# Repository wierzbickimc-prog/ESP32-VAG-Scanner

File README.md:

# ESP32 VAG Scanner

Read older VW and Audi controllers with a cheap KKL USB cable. Scan the car's modules, read
identification, read and clear fault codes, and watch live measuring blocks. It speaks
**KW1281**, the K-line protocol used by VAG cars from about 1990 to 2004.

There are two front ends, both driving the same cable with the same protocol core:

- **macOS**: a SwiftUI app.
- **ESP32-P4**: a standalone touch-screen unit (Guition JC8012P4A1C). The KKL cable plugs
  into the P4's USB port, with no wiring.

> **Status:** tested on a 2002 EuroVan from the Mac: the engine (Motronic ME7.1, 10400 baud)
> and the 01P automatic transmission (1200 baud) read identification, faults and live data.
> The P4 runs on hardware; its first real-car test is under way. Other cars and controllers
> are untested.

## Install on an ESP32-P4 (no tools needed)

Open the **[install page](https://wierzbickimc-prog.github.io/ESP32-VAG-Scanner/)** in Chrome or
Edge, connect the board's USB-serial port, and click **Install**. It uses
[ESP Web Tools](https://esphome.github.io/esp-web-tools/). Each GitHub release builds the firmware
and updates the page automatically (`.github/workflows/firmware.yml`).

## Screenshots

### macOS

| Overview | Fault codes |
|---|---|
|  |  |

Click a fault for everything the controller stores about it:

### ESP32-P4

| Home | Fault codes |
|---|---|
|  |  |

### Dashboard

| macOS | ESP32-P4 |
|---|---|
|  |  |

All screenshots show the simulated EuroVan (demo mode).

## Features

- Open a module directly from the landing screen and automatically read its fault codes,
  without scanning the car first. Both apps show **01 Engine**, **02 Transmission**,
  **03 ABS**, **08 HVAC**, **15 Airbags**, and **17 Instruments**, with **More modules** for
  the remaining known addresses. Identification and faults use one connection.
- Scan for controllers (common addresses, or all of 01-7F).
- Controller identification (part number, component, coding).
- Fault codes with descriptions, OBD-II P-codes, the fault type ("Short to Ground") and the
  intermittent flag. Clearing asks for confirmation first.
- Live measuring blocks, with standard VW labels where known.
- A **four-slot dashboard** with live values and trend charts. The EuroVan default shows
  coolant temperature, battery voltage, ATF temperature and fuel economy. Each slot can show
  a preset, or any field you pin from a controller's Live data (the pin button on the Mac;
  tap the value on the P4). US or metric units.
- Fault codes link to the **Ross-Tech wiki**. The Mac opens the page in the browser. The P4
  shows a QR code, and with **Wi-Fi** (through the board's ESP32-C6) reads the page itself.
- **Fuel economy** estimated from the engine's air mass and vehicle speed (VW standard groups
  2 and 5, assuming a stoichiometric mixture), with instant and trip average. On the Mac,
  **Calibrate** scales the estimate to match the fuel actually pumped at a fill-up.
- Recognises a few specific cars from their part numbers (T4 EuroVan, Mk3 Golf) and shows a
  matching photo.
- Demo mode with simulated cars, so you can try it without a car or cable.
- **EuroVan health checks** on both apps: a guided 01P ATF level assistant,
  AXK camshaft timing/chain assessment, misfire-counter monitoring and an ECU
  supply-voltage check. Each shows its prerequisites, readings, limitations and
  factory procedure source, and can save a local snapshot. See
  [procedures and validation status](docs/health-checks.md).

Connecting the cable does not start vehicle communication. Tap **Scan car** or a
module card to begin; the ESP32 also stays idle if its display cannot initialize.

The **Scan car** button still discovers controllers as before. Module cards start at
**Not checked** and update after a read; a missing controller shows **No response** rather
than a clean fault result. Not every car has every controller. Addresses use hexadecimal
notation (for example, **17** means instruments).

**Dashboard notes.** KW1281 talks to one controller at a time, and switching costs a 2–3 s
wake-up. The dashboard reads each controller several times before switching, so slots on
the engine update continuously while the transmission's ATF temperature updates every few
seconds. The ATF preset uses **02, group 5, field 1**, verified on the EuroVan's 01P.
Some other transmissions use group 2 or 4: open **02 Auto Trans → Live data**,
find the temperature, and pin it to the slot if it differs.
You can start the dashboard directly without opening a module or scanning first.
Its first connection to each controller retries wake-up and searches the supported
baud rates even if no sync byte arrives. This initial discovery can take longer
than a normal controller switch; absent controllers get a short retry on later visits.
Tiles show connection status and the age of the last successful sample, including
when a failed read leaves the previous value displayed.
The fuel estimate can't see overrun fuel cut-off, so calibrate it after a fill-up.

For connection diagnostics on the Mac, run `KW_TRACE=1 swift run ESP32VAGScanner`
from `mac/`. The trace includes address, attempted baud, cached baud, sync byte
or timeout, handshake/identification phase, and error code. The P4 emits these
connection diagnostics in its serial monitor, plus measuring-group failures.

KW1281 controllers store only a fault code and one status byte. There's no mileage,
occurrence count or freeze-frame data; that arrived with KWP2000 and UDS, which this tool
doesn't support.

**Health checks.** Open **Health checks** in the Mac sidebar or **EuroVan health
checks** on the P4 home screen. Choose a check, Start, then confirm the physical
conditions for that run. The ATF assistant requires a cold start around 30°C or
below and guides a physical overflow inspection at 35–45°C; the app cannot
measure fluid level. Timing screening applies the verified AXK intake limits and
shows the exhaust offset and difference as observations. It does not certify
chain or guide condition. Checks are restricted to engine `022906032AF` and
transmission `01P927733CG`; new health groups still await real-vehicle validation.

## Hardware

- A **KKL USB cable with an FTDI chip** (`0403:6001`, FT232R/BM). Tested cable: "USB <-> Serial",
  no serial number.
- For the standalone unit: a **Guition JC8012P4A1C** (ESP32-P4, 10.1" 800x1280 touch screen).

## Layout

| Path | What |
|---|---|
| [`kwcore/`](kwcore) | KW1281 protocol in plain C99, a simulated ECU, tests, and the `kwcli` command-line tool |
| [`mac/`](mac) | SwiftUI app. It links `kwcore` through symlinks in `Sources/KWCore` |
| [`esp32/`](esp32) | ESP-IDF project: USB host FTDI driver, LVGL UI. See [`esp32/README.md`](esp32/README.md) |
| [`hardware/kline-dongle/`](hardware/kline-dongle) | Unbuilt ESP32-C3 K-line dongle prototype; circuit, PCB, and assembly notes. Dedicated firmware is pending |
| [`assets/`](assets) | Car photos, measuring-block labels, and the scripts that build and fetch them |
| [`kw1281test/`](https://github.com/gmenounos/kw1281test) | Submodule: the upstream C# tool this protocol code is checked against |
| [`HANDOVER.md`](HANDOVER.md) | Design decisions, verified facts, and next steps |

## Build and run

```sh
git clone --recursive https://github.com/wierzbickimc-prog/ESP32-VAG-Scanner.git
cd ESP32-VAG-Scanner
```

**Protocol tests and command-line tool**

```sh
make -C kwcore test
make -C kwcore kwcli
kwcore/kwcli /dev/cu.usbserial-XXXX scan
kwcore/kwcli /dev/cu.usbserial-XXXX faults 01   # addresses are hex: 17 = instruments
KW_TRACE=1 kwcore/kwcli /dev/cu.usbserial-XXXX ident 01   # log every byte
```

**macOS app** (macOS 13+, Swift 5.9+)

```sh
cd mac
swift run ESP32VAGScanner                   # pick the cable in the app
swift run ESP32VAGScanner --demo            # straight into the simulated EuroVan
swift run ESP32VAGScanner --demo=golf --overview
swift run ESP32VAGScanner --demo --dashboard  # simulated EuroVan, dashboard running
swift run ESP32VAGScanner --demo --health     # EuroVan health-check screen
```

Direct-module integration tests use the simulated cars and require Xcode's XCTest framework:

```sh
DEVELOPER_DIR=/Applications/Xcode.app/Contents/Developer swift test --package-path mac
```

**ESP32-P4** (ESP-IDF v5.5.6)

```sh
. ~/esp/esp-idf-v5.5/export.sh
cd esp32
idf.py build
idf.py -p /dev/cu.usbserial-XXXX flash monitor   # the board's CH340 port
```

On the P4, hold **Scan** to open the demo cars. **Dashboard** sits between Scan and Demo. The
Wi-Fi button at the top opens the Wi-Fi screen; Wi-Fi is only used for the wiki viewer.

## Optional data (not in this repo)

Both apps work without these. With them, faults get descriptions and type text. Released P4
firmware includes the fault type names but never the Ross-Tech descriptions; it reads those
from the Ross-Tech wiki over Wi-Fi instead.

- **Fault descriptions:** a `code,meaning` CSV saved as `ross-tech-fault-codes.csv` in the repo
  root (the P4 build embeds it), and on the Mac as
  `~/Library/Application Support/ESP32 VAG Scanner/fault-codes.csv`.
- **Fault type names:** `python3 assets/tools/fetch_fault_types.py` downloads the list from
  [KLineKWP1281Lib_ESP32](https://github.com/domnulvlad/KLineKWP1281Lib_ESP32) (GPL-3.0) at a
  pinned commit into `kwcore/fault_types.h`. On the Mac, run `touch kwcore/fault_table.c` before
  the next build so it picks the file up.

## License

GNU General Public License v3.0 (see [`LICENSE`](LICENSE)): use it, share it, and change it
freely, and pass the same freedom on with anything you distribute. The fault type names come
from GPL-3.0 code. Bundled third-party parts keep their own licences (MIT and Apache-2.0, all
compatible), and the car photos are CC-licensed as listed in `assets/CREDITS.md`. Not affiliated
with Volkswagen or Ross-Tech.

## Credits

- Protocol behaviour follows [kw1281test](https://github.com/gmenounos/kw1281test) by Greg
  Menounos (MIT).
- Display and touch drivers are vendored from
  [chipguyhere/JC8012P4A1C_display](https://github.com/chipguyhere/JC8012P4A1C_display) (MIT).
- Fault type names come from [KLineKWP1281Lib_ESP32](https://github.com/domnulvlad/KLineKWP1281Lib_ESP32)
  by domnulvlad (GPL-3.0); header+body measuring-group formulas follow the same library.
- Car photos come from Wikimedia Commons; authors and licences are in
  [`assets/CREDITS.md`](assets/CREDITS.md) and shown in both apps.

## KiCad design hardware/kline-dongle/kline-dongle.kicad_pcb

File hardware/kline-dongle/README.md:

# K-line dongle (revision 3 prototype)

A 58 × 24 mm, two-layer carrier for a Seeed XIAO ESP32C3 and an ST L9637D
K-line transceiver, in a 3D-printed case. Open `kline-dongle.kicad_pro` in KiCad 10.

**Status: unbuilt prototype.** ERC, DRC and schematic parity are clean, and the case
has been checked against the board's 3D model. Nothing has been built. Bench
operation, case fit and tolerances, automotive transients, temperature and RF
performance are not validated. This is a **12 V vehicle design**: don't use it on a
24 V vehicle or assume it survives a 24 V jump start.

**Firmware is still required.** The repository's ESP32 firmware targets the P4
display and an FTDI cable; it does not run on this C3 dongle. A direct-UART `KwIo`,
battery measurement and a BLE/Wi-Fi link are still to be written. The pin table
below is their hardware interface.

## Revision 3 changes

- **U1 lies flat.** The upright R-78HB stood 17.5 mm tall; the horizontal
  R-78HB5.0-0.5L is 8.6 mm, so the populated board is about 10 mm tall.
- **No J2 jumper.** The XIAO is fed through D3, as Seeed recommends for the 5 V pad.
  USB can stay connected in the car; there is no shunt to fit or forget.
- **Simple battery sense.** A 100k/10k divider (0.11 mA) replaces the 10k/1k
  divider, zener, CBTLV switch and their resistors, which together drew about
  1.15 mA from the always-live OBD pin. GPIO6 is free.
- **R12 removed** (3.3 V bleed, 0.33 mA).
- Kept from revision 2: Q1/R10/R11 hold the K-line released while the ESP32 is off
  or resetting; U6 is the 5 V-tolerant RX buffer; D2 is SMBJ18CA.

## Assembly

**JLCPCB (cheaper, about $50–55 for 5 boards before shipping).** JLCPCB solders all
the surface-mount parts from its own stock; you then solder the XIAO, the converter
and the OBD wires. See [JLCPCB instructions](JLC-ASSEMBLY.md). The BOM below uses
parts JLCPCB stocks, so the same files serve both routes.

**Seeed Studio (about $300+ for 5).** Seeed supplies and assembles the complete populated board, including U1, the XIAO
and the antenna attachment. You only wire the OBD cable and fit the case. **J1 stays
unpopulated** as four plated wire holes. See [Seeed upload instructions](SEEED-ASSEMBLY.md)
and the [factory assembly/test notes](FACTORY-NOTES.md).

## USB and car power together

D3 keeps USB VBUS out of the 5 V converter, so USB can be plugged in while the dongle
is on the car. The reverse is not blocked: with the car connected, the XIAO's 5 V pad
(about 4.7 V through D3) also appears on the USB cable's VBUS. A powered computer
holds VBUS at 5 V and nothing flows; a switched-off one may be back-fed. Use a
powered computer, or unplug the OBD cable, when debugging over USB.

## Case

A base and a lid, printed separately (`enclosure/base.stl`, `enclosure/lid.stl`,
already in print orientation). Outside: **63 × 29 × 17.4 mm**.

- The board drops onto two ledges along its long edges. The lid's lip fits inside
  the walls and its posts hold the board, the XIAO and the converter down.
- **The car connects through an OBD-II male pigtail cable** (16-pin male plug with
  loose wires) entering the left end through a 6.5 mm hole. Solder plug pins 16, 4,
  5 and 7 to J1 (silkscreen labels). Put a zip tie round the cable just inside the
  wall as a strain-relief stop. A board this size with a 10 mm part doesn't fit
  inside a standard OBD plug shell.
- USB-C is open at the right end; a 2.5 mm hole over D5 shows the status LED.
- Stick the XIAO's flexible antenna inside the lid, away from the converter.
- The lid is a press fit. Clearance is 0.2 mm per side (`LIP_CLR`); add tape or a drop
  of glue if it rattles, or adjust and reprint.
- PETG or ASA: PLA softens in a parked car.

To change the case, edit the parameters at the top of `enclosure/enclosure.py`
(cable diameter, clearances, wall thickness). It reads part positions from
`gen/place.py`, so the openings follow the board.

```sh
cd enclosure
python3 -m pip install manifold3d numpy trimesh matplotlib
python3 enclosure.py                       # base.stl, lid.stl
kicad-cli pcb export glb --subst-models -o board.glb ../kline-dongle.kicad_pcb
python3 render.py board.glb                # renders/*.png
```

## Files and regeneration

| File | Purpose |
|---|---|
| `kline-dongle.kicad_sch` / `.kicad_pcb` | Schematic and routed board |
| `dongle.kicad_sym`, `sym-lib-table` | Project symbols |
| `dongle.pretty/`, `fp-lib-table` | Local XIAO footprint with carrier-compatible silkscreen |
| `dongle.3dshapes/XIAO_ESP32C3.wrl` | Approximate XIAO 3D model (from `gen/xiao_model.py`) |
| `gen/parts.py`, `gen/place.py` | Parts, connections and placement source |
| `gen/build_sch.py`, `gen/build_pcb.py` | Schematic and PCB generators |
| `gen/check_export.py` | ERC, DRC/parity, Seeed BOM/CPL and upload ZIPs |
| `enclosure/` | Case generator, STLs and renders |
| `JLC-ASSEMBLY.md`, `SEEED-ASSEMBLY.md`, `FACTORY-NOTES.md` | Upload and factory assembly/test instructions |
| `build/` | Generated reports and manufacturing files; ignored by Git |

Run from this directory:

```sh
python3 gen/build_sch.py
/Applications/KiCad/KiCad.app/Contents/Frameworks/Python.framework/Versions/3.9/bin/python3 gen/build_pcb.py
python3 gen/check_export.py
```

`build_pcb.py` needs KiCad's `pcbnew` and `wx` Python modules. On other systems,
use their KiCad Python interpreter and set `KICAD_FOOTPRINT_DIR` to the installed
footprint directory if needed. `KICAD_CLI` can override the CLI executable. If a
net fails to route, set `KLINE_DEBUG_PCB=/tmp/debug.kicad_pcb` to save the partial
board for inspection.

Regeneration overwrites schematic/PCB edits. Make changes in the generators, or stop
regenerating once you start editing the design by hand. Always run the checks after
regeneration; a completed route is not electrical validation.

## Bill of materials

Part numbers and LCSC/JLCPCB numbers are in `gen/parts.py`. Use the exact ICs/packages specified; AHCT, LVC and LIN devices are not
interchangeable. `build/fabrication/bom-detail.csv` includes references and datasheets.

| Ref | Part / specification | Package | Notes |
|---|---|---|---|
| U1 | RECOM R-78HB5.0-0.5L | SIP-3, horizontal | 9–72 V in; 5 V, 0.5 A out; 8.6 mm above the board |
| U2 | ST L9637D | SOIC-8, 3.9 × 4.9 mm | No TX timeout; LIN transceivers can truncate the 5-baud wake-up |
| U3 | TI SN74AHCT1G125DBVR | SOT-23-5 | TX level shift |
| U4 | Seeed XIAO ESP32C3 | Castellated module | Include its external U.FL antenna |
| U6 | TI SN74LVC1G17DCKR | SC70-5 | 5 V tolerant RX buffer, Ioff protection |
| F1 | BHFUSE BSMD1812-050-60V (or Bourns MF-MSMF050/60X-2) | 1812 | PTC, 0.5 A hold, 60 V |
| D1 | SS14, 40 V / 1 A | SMA | Reverse polarity; D2 keeps it below 30 V |
| D2 | SMBJ18CA | SMB | 18 V bidirectional TVS, 29.2 V maximum clamp |
| D3 | B5819WS, 40 V / 1 A | SOD-323 | Keeps USB VBUS out of the converter |
| D5 | Green LED | 0603 | Status |
| Q1 | 2N7002 (or BSS138) | SOT-23 | TX buffer enable: pad 1 gate, 2 source, 3 drain |
| R1 | 510 Ω, 5%, 1 W | 2512 | K-line pull-up; about 0.5 W with 16 V across it |
| R3, R7, R10 | 10 kΩ, 1% | 0603 | |
| R4 | 1 kΩ, 1% | 0603 | |
| R6 | 100 kΩ, 1% | 0603 | Battery divider, upper |
| R11 | 100 kΩ, 1% | 0603 | Q1 gate pull-down |
| C1 | 10 µF, 50 V, X7R | 1210 | |
| C2 | 100 nF, 50 V, X7R | 0603 | U2 VS decoupling |
| C3 | 10 µF, 25 V, X5R | 0805 | Converter output |
| C4, C5, C6, C8 | 100 nF, 50 V, X7R | 0603 | Decoupling / ADC filter |
| J1 | Bare wire holes; no header | 2.54 mm through-hole | OBD pigtail wires: 16, 4, 5, 7 |
| TP1–TP8 | PCB copper only | Back-side 1 mm pads | No purchased component |

The local XIAO footprint derives from KiCad's `RF_Module:MCU_Seeed_ESP32C3`
(CC BY-SA 4.0 with the KiCad libraries exception); its front silkscreen is adapted
for this carrier. Its unused underside pads remain isolated copper islands.

## MCU interface and battery calculation

| GPIO | XIAO pad | Use |
|---|---|---|
| 4 | D2 | UART1 TX; R3 holds it high during reset |
| 5 | D3 | UART1 RX, including the local TX echo |
| 3 | D1 | ADC1 channel 3 battery sense |
| 7 | D5 | `TX_EN`: HIGH enables U3 through Q1; reset/LOW releases the K-line |
| 10 | D10 | Status LED |
| 6 | D4 | Free |

Firmware must keep GPIO7 low until UART1 is configured with TX idle high, then set
GPIO7 high to enable TX. Return GPIO7 low before sleep.

```text
VBAT = calibrated_ADC_volts × 11      (100k / 10k)
```

12.6 V reads 1.15 V; the TVS's 29.2 V maximum clamp reads 2.65 V, inside the ADC
pin's rating, and R6 limits any fault current into the pin. Use the ESP32-C3's
calibrated ADC conversion with 11 dB attenuation. VBAT is measured **after D1**, so
the OBD supply is higher by D1's load-dependent drop.

The 5-baud wake-up drives GPIO4 directly as a GPIO for its 200 ms bits, then hands
the pin back to UART1. USB Serial/JTAG is for programming and debugging, not an
FTDI-compatible cable endpoint.

## Fabrication constraints

2-layer FR-4, 1.6 mm, 1 oz finished copper, 0.2 mm minimum track/clearance, 0.3 mm
via drill, 0.6 mm via diameter, 0.5 mm copper-to-edge. The USB-C/module courtyard
overhang past the board edge is intentional. `check_export.py` fails on any ERC/DRC
warning, schematic parity issue or BOM/placement mismatch before exporting Gerbers,
drill files, the Seeed BOM/CPL, PDFs and factory instructions. The exports are
prototype artifacts, not proof that the design is qualified.

## Bring-up and outstanding validation

1. USB disconnected. Apply a 12 V bench supply at J1, current-limited to 250 mA.
   Check 5 V at TP2, 3.3 V at TP3, TP8 ≈ TP1/11, and K-line idle high at TP4.
2. Flash bring-up firmware over USB (bench power may stay on). Verify TX/K/RX levels,
   5-baud timing, echo, baud changes and the ADC scaling against a meter.
3. Verify the K-line stays released during reset, bootloader entry, sleep and power
   transitions. On these VWs the immobilizer can share the K-line: confirm the
   engine starts with the dongle plugged in, in every state.
4. Run the fake-ECU loopback with a powered KKL cable and common ground, then a
   controlled vehicle test after the bench checks pass.
5. Print the case and check the fit, the USB plug and the LED window.

U1 needs at least 9 V after D1, so cranking may reset the dongle. OBD pin 16 is
always live: the converter's and transceiver's quiescent current, plus 0.11 mA for
the divider, flow even while the ESP32 sleeps. Measure it, and unplug the dongle for
long storage.

Surge/load-dump energy, TVS temperature, PTC fault coordination, D1 reverse-voltage
margin, K-line ESD and emissions have not been tested against automotive pulse
requirements. A 600 W TVS's short-pulse rating does not prove survival of a long
load dump.

## Primary references

- [ST L9637 pinout, thresholds and limits](https://www.st.com/resource/en/datasheet/l9637.pdf)
- [Diodes SMBJ18CA ratings](https://www.diodes.com/part/view/SMBJ18CA)
- [Bourns MF-MSMF fuse ratings and derating](https://www.bourns.com/docs/product-datasheets/mf-msmf.pdf)
- [RECOM R-78HB-0.5L dimensions and application guidance](https://www.recom-power.com/pdf/Innoline/R-78HBxx-0.5_L.pdf)
- [Seeed XIAO ESP32C3 power circuit](https://files.seeedstudio.com/wiki/XIAO_WiFi/Resources/Seeeduino-XIAO-ESP32C3-SCH.pdf)
- [Espressif ESP32-C3 ADC and electrical limits](https://www.espressif.com/sites/default/files/documentation/esp32-c3_datasheet_en.pdf)

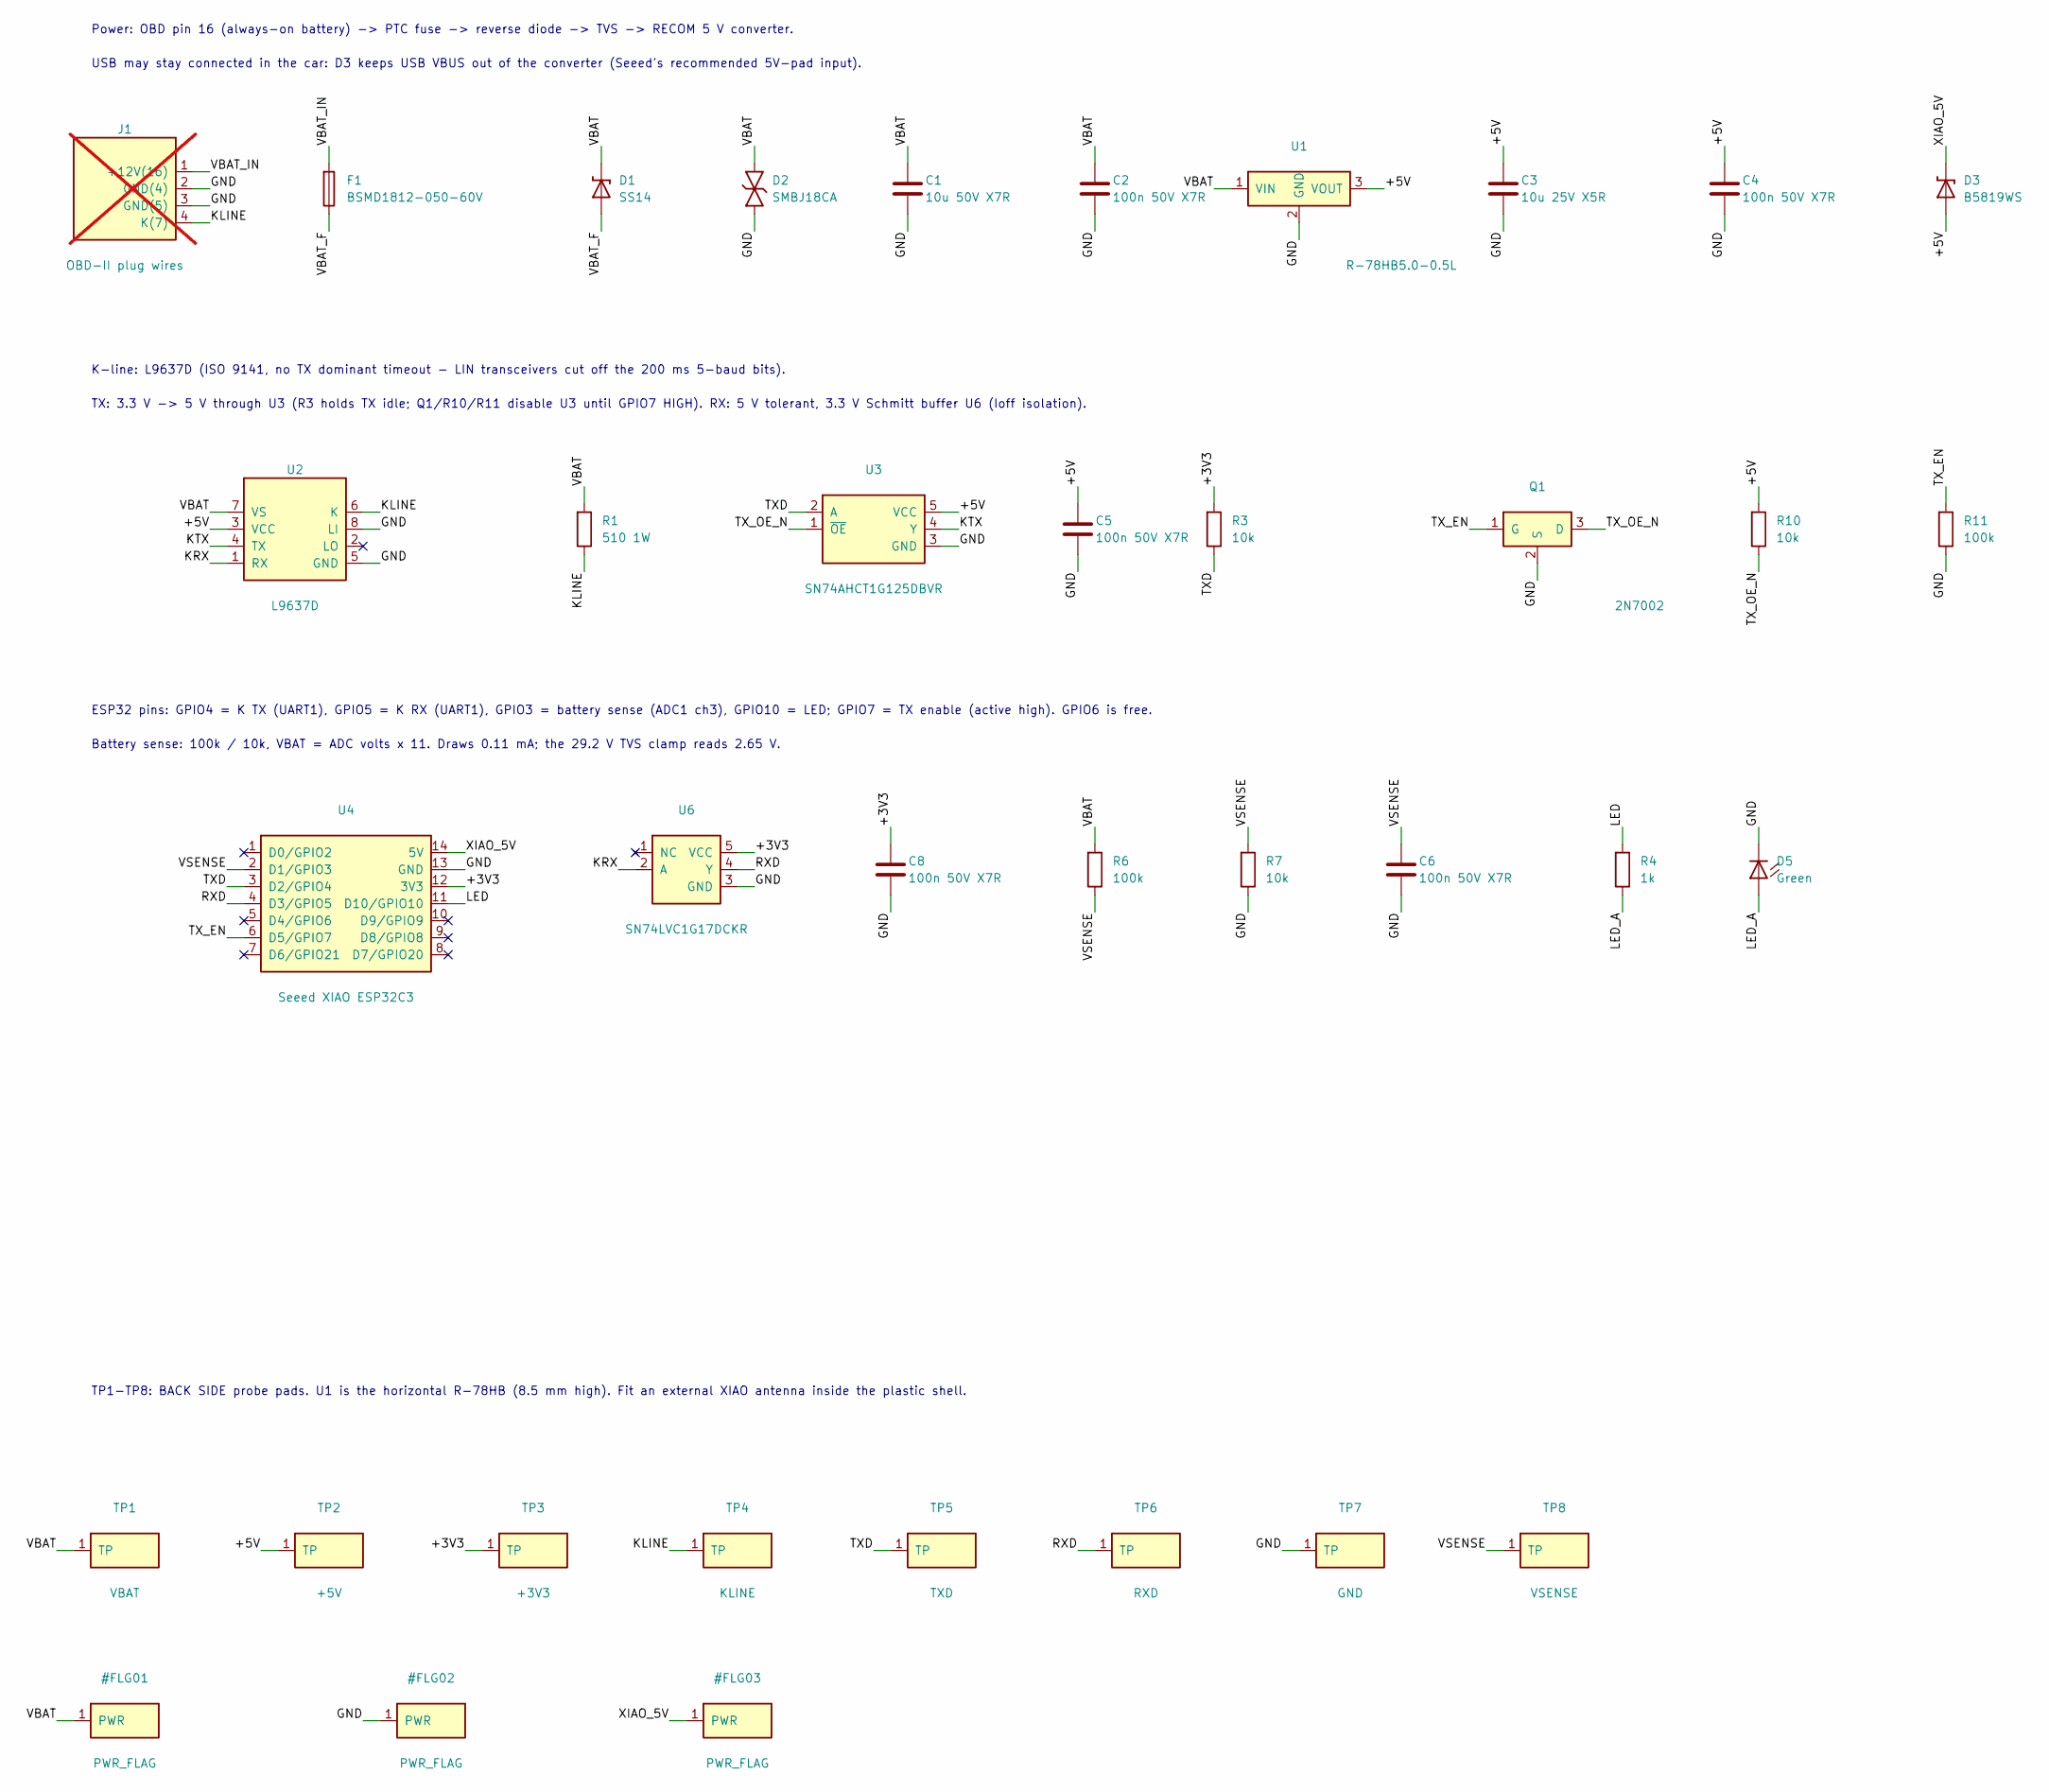
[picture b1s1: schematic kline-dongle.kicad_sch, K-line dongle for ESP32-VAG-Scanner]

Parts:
C1: 10u 50V X7R; C_1210_3225Metric; MPN GRM32ER71H106KA12L; LCSC C77102
C2, C4, C5, C6, C8: 100n 50V X7R; C_0603_1608Metric; MPN CC0603KRX7R9BB104; LCSC C14663
C3: 10u 25V X5R; C_0805_2012Metric; MPN CL21A106KAYNNNE; LCSC C15850
D1: SS14; D_SMA; MPN SS14; LCSC C2480
D2: SMBJ18CA; D_SMB; MPN SMBJ18CA; LCSC C113991
D3: B5819WS; D_SOD-323; MPN B5819WS; LCSC C64886
D5: Green; LED_0603_1608Metric; MPN LTST-C190KGKT; LCSC C125094
F1: BSMD1812-050-60V; Fuse_1812_4532Metric; MPN BSMD1812-050-60V; LCSC C883142
J1: OBD-II plug wires; PinHeader_1x04_P2.54mm_Vertical; not fitted
Q1: 2N7002; SOT-23; MPN 2N7002; LCSC C8545
R1: 510 1W; R_2512_6332Metric; MPN 25121WJ0511T4E; LCSC C36171
R3, R7, R10: 10k; R_0603_1608Metric; MPN 0603WAF1002T5E; LCSC C25804
R4: 1k; R_0603_1608Metric; MPN 0603WAF1001T5E; LCSC C21190
R6, R11: 100k; R_0603_1608Metric; MPN 0603WAF1003T5E; LCSC C25803
TP1: VBAT; TestPoint_Pad_D1.0mm
TP2: +5V; TestPoint_Pad_D1.0mm
TP3: +3V3; TestPoint_Pad_D1.0mm
TP4: KLINE; TestPoint_Pad_D1.0mm
TP5: TXD; TestPoint_Pad_D1.0mm
TP6: RXD; TestPoint_Pad_D1.0mm
TP7: GND; TestPoint_Pad_D1.0mm
TP8: VSENSE; TestPoint_Pad_D1.0mm
U1: R-78HB5.0-0.5L; Converter_DCDC_RECOM_R-78HB-0.5L_THT; MPN R-78HB5.0-0.5L
U2: L9637D; SOIC-8_3.9x4.9mm_P1.27mm; MPN E-L9637D013TR; LCSC C153038
U3: SN74AHCT1G125DBVR; SOT-23-5; MPN SN74AHCT1G125DBVR; LCSC C7484
U4: Seeed XIAO ESP32C3; XIAO_ESP32C3_Carrier; MPN 113991054
U6: SN74LVC1G17DCKR; SOT-353_SC-70-5; MPN SN74LVC1G17DCKR; LCSC C10425

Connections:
/+3V3: C8.1, R3.1, TP3.1, U4.12 (3V3), U6.5 (VCC)
/+5V: C3.1, C4.1, C5.1, D3.2 (A), R10.1, TP2.1, U1.3 (VOUT), U2.3 (VCC), U3.5 (VCC)
/GND: C1.2, C2.2, C3.2, C4.2, C5.2, C6.2, C8.2, D2.2 (A2), D5.1 (K), J1.2 (GND(4)), J1.3 (GND(5)), Q1.2 (S), R7.2, R11.2, TP7.1, U1.2 (GND), U2.5 (GND), U2.8 (LI), U3.3 (GND), U4.13 (GND), U6.3 (GND)
/KLINE: J1.4 (K(7)), R1.2, TP4.1, U2.6 (K)
/KRX: U2.1 (RX), U6.2 (A)
/KTX: U2.4 (TX), U3.4 (Y)
/LED: R4.1, U4.11 (D10/GPIO10)
/LED_A: D5.2 (A), R4.2
/RXD: TP6.1, U4.4 (D3/GPIO5), U6.4 (Y)
/TXD: R3.2, TP5.1, U3.2 (A), U4.3 (D2/GPIO4)
/TX_EN: Q1.1 (G), R11.1, U4.6 (D5/GPIO7)
/TX_OE_N: Q1.3 (D), R10.2, U3.1 (~OE)
/VBAT: C1.1, C2.1, D1.1 (K), D2.1 (A1), R1.1, R6.1, TP1.1, U1.1 (VIN), U2.7 (VS)
/VBAT_F: D1.2 (A), F1.2
/VBAT_IN: F1.1, J1.1 (+12V(16))
/VSENSE: C6.1, R6.2, R7.1, TP8.1, U4.2 (D1/GPIO3)
/XIAO_5V: D3.1 (K), U4.14 (5V)

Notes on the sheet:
TP1-TP8: BACK SIDE probe pads. U1 is the horizontal R-78HB (8.5 mm high). Fit an external XIAO antenna inside the plastic shell.
Power: OBD pin 16 (always-on battery) -> PTC fuse -> reverse diode -> TVS -> RECOM 5 V converter.
USB may stay connected in the car: D3 keeps USB VBUS out of the converter (Seeed's recommended 5V-pad input).
K-line: L9637D (ISO 9141, no TX dominant timeout - LIN transceivers cut off the 200 ms 5-baud bits).
TX: 3.3 V -> 5 V through U3 (R3 holds TX idle; Q1/R10/R11 disable U3 until GPIO7 HIGH). RX: 5 V tolerant, 3.3 V Schmitt buffer U6 (Ioff isolation).
ESP32 pins: GPIO4 = K TX (UART1), GPIO5 = K RX (UART1), GPIO3 = battery sense (ADC1 ch3), GPIO10 = LED; GPIO7 = TX enable (active high). GPIO6 is free.
Battery sense: 100k / 10k, VBAT = ADC volts x 11. Draws 0.11 mA; the 29.2 V TVS clamp reads 2.65 V.

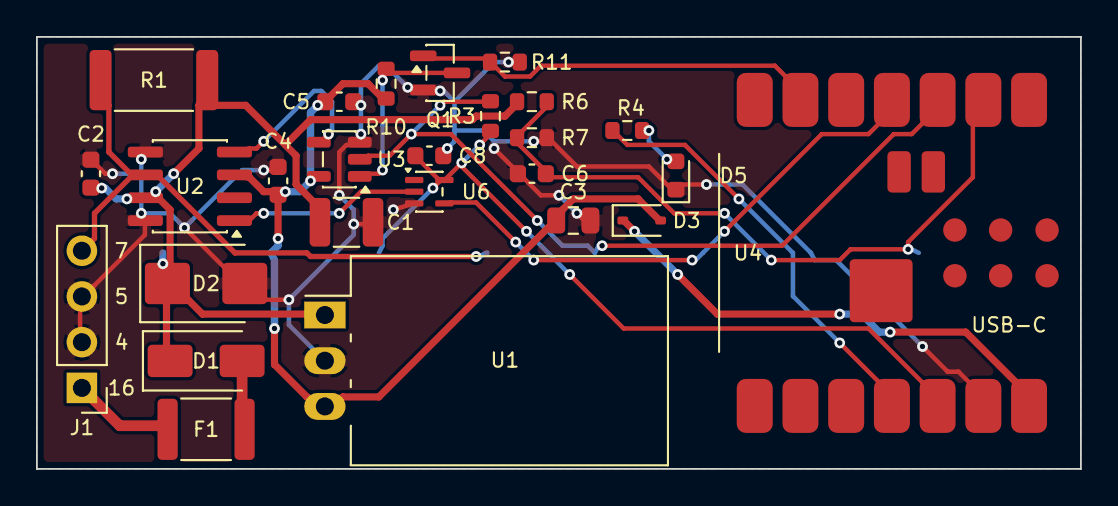
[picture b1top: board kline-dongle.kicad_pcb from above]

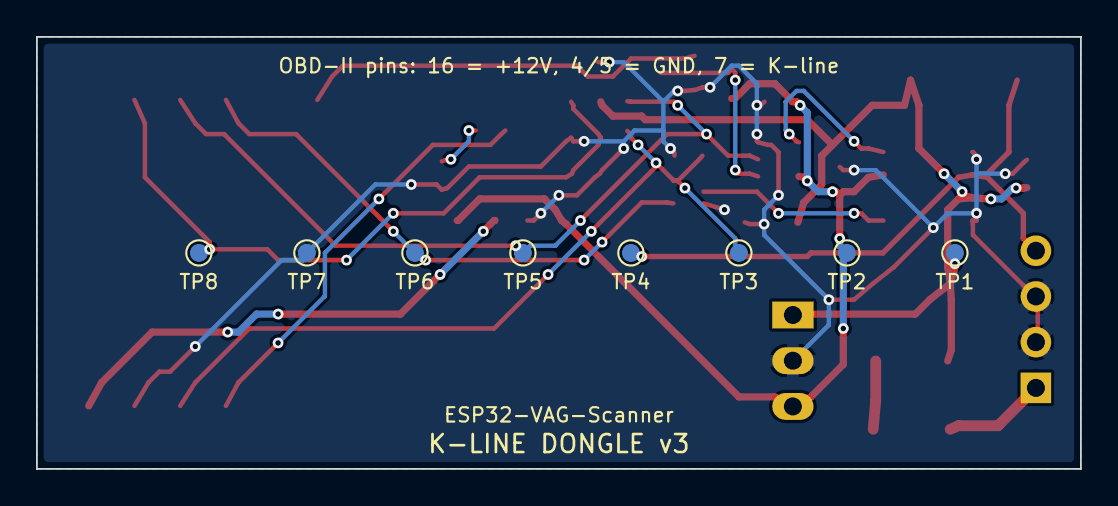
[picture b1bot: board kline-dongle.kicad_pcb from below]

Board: 2 copper layers, 58.0 x 24.0 mm, 34 parts (8 on the bottom side), 17 nets.
